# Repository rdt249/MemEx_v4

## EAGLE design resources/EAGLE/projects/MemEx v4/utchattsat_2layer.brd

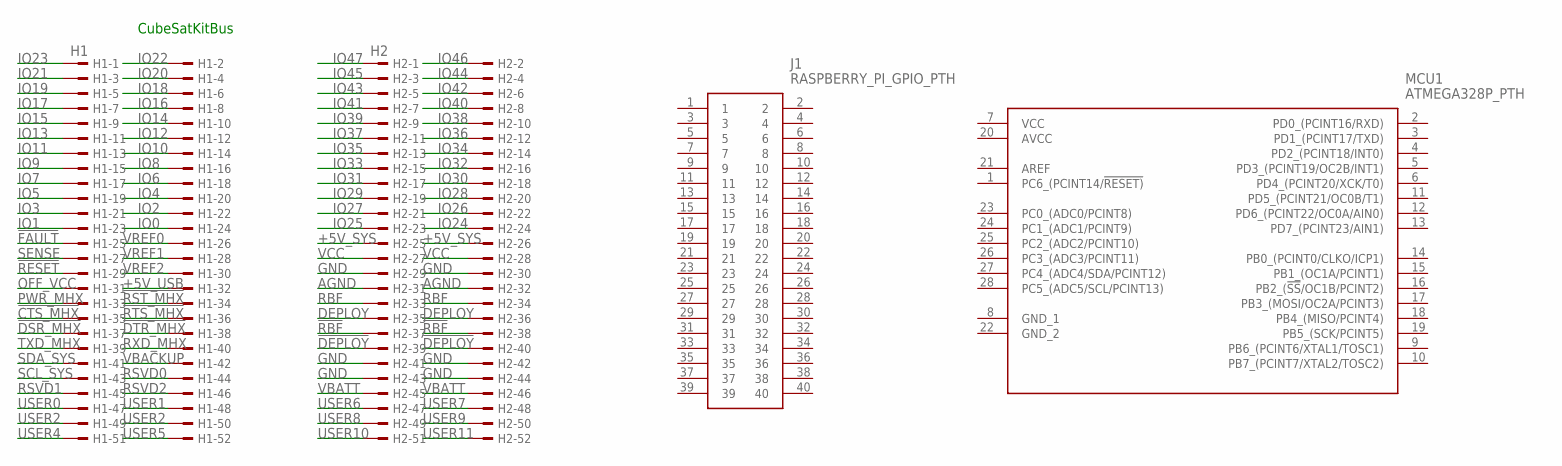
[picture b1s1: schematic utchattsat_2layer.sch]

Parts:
H1: H1; TSW-126-XX-G-D
H2: H2; TSW-126-XX-G-D
J1: RASPBERRY_PI_GPIO_PTH; RHDR40W64P254_2X20_5130X500X13
MCU1: ATMEGA328P_PTH; DIP794W53P254L3467H457Q28N

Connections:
!CTS_MHX: H1.35
!DEPLOY: H2.39, H2.40
!DSR_MHX: H1.37
!DTR_MHX: H1.38
!FAULT: H1.25
!RBF: H2.37, H2.38
!RESET: H1.29
!RST_MHX: H1.34
!RTS_MHX: H1.36
+5V_SYS: H2.25, H2.26
+5V_USB: H1.32
AGND: H2.31, H2.32
DEPLOY: H2.35, H2.36
GND: H2.29, H2.30, H2.41, H2.42, H2.43, H2.44
IO0: H1.24
IO1: H1.23
IO2: H1.22
IO3: H1.21
IO4: H1.20
IO5: H1.19
IO6: H1.18
IO7: H1.17
IO8: H1.16
IO9: H1.15
IO10: H1.14
IO11: H1.13
IO12: H1.12
IO13: H1.11
IO14: H1.10
IO15: H1.9
IO16: H1.8
IO17: H1.7
IO18: H1.6
IO19: H1.5
IO20: H1.4
IO21: H1.3
IO22: H1.2
IO23: H1.1
IO24: H2.24
IO25: H2.23
IO26: H2.22
IO27: H2.21
IO28: H2.20
IO29: H2.19
IO30: H2.18
IO31: H2.17
IO32: H2.16
IO33: H2.15
IO34: H2.14
IO35: H2.13
IO36: H2.12
IO37: H2.11
IO38: H2.10
IO39: H2.9
IO40: H2.8
IO41: H2.7
IO42: H2.6
IO43: H2.5
IO44: H2.4
IO45: H2.3
IO46: H2.2
IO47: H2.1
OFF_VCC: H1.31
PWR_MHX: H1.33
RBF: H2.33, H2.34
RSVD0: H1.44
RSVD1: H1.45
RSVD2: H1.46
RXD_MHX: H1.40
SCL_SYS: H1.43
SDA_SYS: H1.41
SENSE: H1.27
TXD_MHX: H1.39
USER0: H1.47
USER1: H1.48
USER2: H1.49, H1.50
USER4: H1.51
USER5: H1.52
USER6: H2.47
USER7: H2.48
USER8: H2.49
USER9: H2.50
USER10: H2.51
USER11: H2.52
VBACKUP: H1.42
VBATT: H2.45, H2.46
VCC: H2.27, H2.28
VREF0: H1.26
VREF1: H1.28
VREF2: H1.30

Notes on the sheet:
CubeSatKitBus

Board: 2 copper layers, 4 parts (2 on the bottom side), 10 nets, no tracks yet.

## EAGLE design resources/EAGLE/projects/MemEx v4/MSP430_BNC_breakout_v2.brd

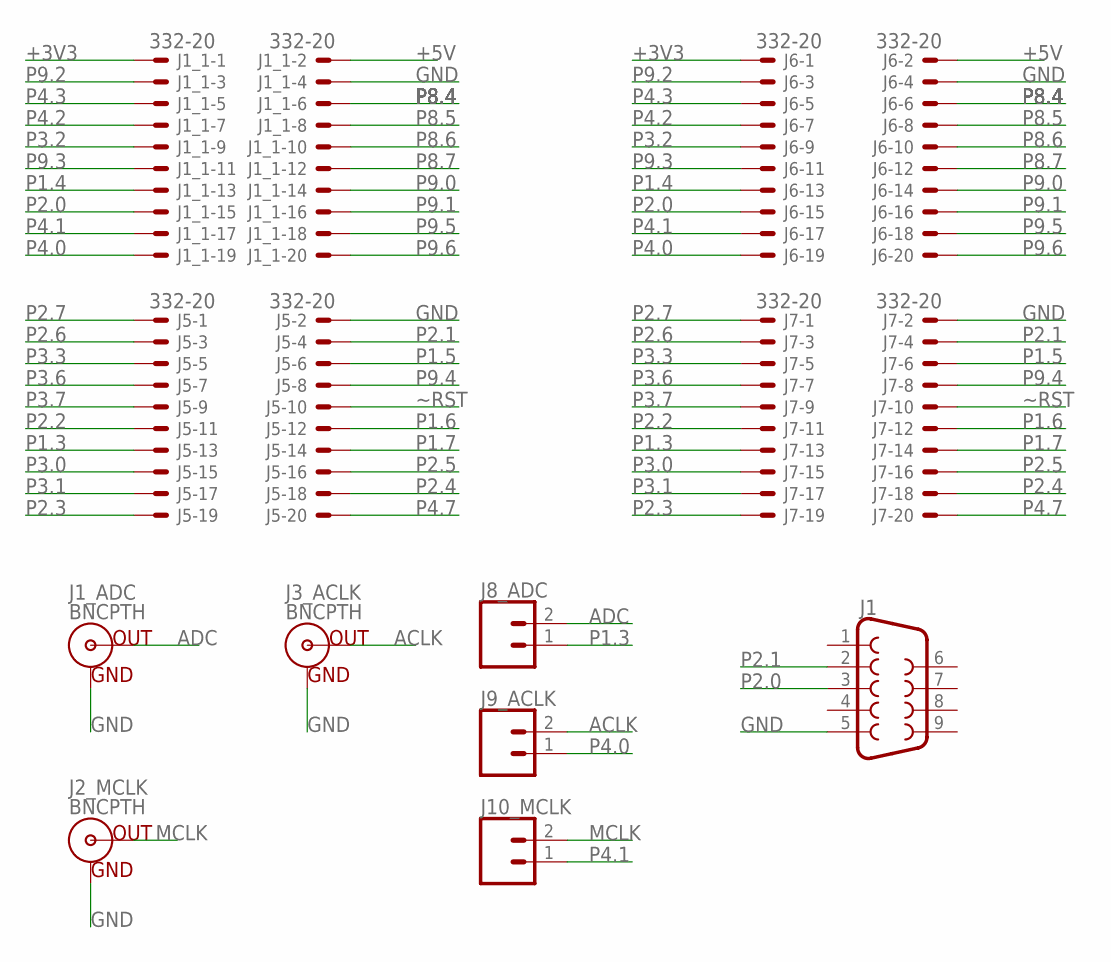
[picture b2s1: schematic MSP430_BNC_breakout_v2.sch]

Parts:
J1: DB9FEMALE; DB9
J1_1, J5, J6, J7: 332-20
J1_ADC, J2_MCLK, J3_ACLK: BNCPTH; BNC
J8_ADC, J9_ACLK, J10_MCLK: CONN_02; 1X02

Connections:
+3V3: J1_1.1, J6.1
+5V: J1_1.2, J6.2
ACLK: J3_ACLK.S (OUT), J9_ACLK.2
ADC: J1_ADC.S (OUT), J8_ADC.2
GND: J1.5, J1_1.4, J1_ADC.GND, J2_MCLK.GND, J3_ACLK.GND, J5.2, J6.4, J7.2
MCLK: J2_MCLK.S (OUT), J10_MCLK.2
P1.3: J5.13, J7.13, J8_ADC.1
P1.4: J1_1.13, J6.13
P1.5: J5.6, J7.6
P1.6: J5.12, J7.12
P1.7: J5.14, J7.14
P2.0: J1.3, J1_1.15, J6.15
P2.1: J1.2, J5.4, J7.4
P2.2: J5.11, J7.11
P2.3: J5.19, J7.19
P2.4: J5.18, J7.18
P2.5: J5.16, J7.16
P2.6: J5.3, J7.3
P2.7: J5.1, J7.1
P3.0: J5.15, J7.15
P3.1: J5.17, J7.17
P3.2: J1_1.9, J6.9
P3.3: J5.5, J7.5
P3.6: J5.7, J7.7
P3.7: J5.9, J7.9
P4.0: J1_1.19, J6.19, J9_ACLK.1
P4.1: J1_1.17, J6.17, J10_MCLK.1
P4.2: J1_1.7, J6.7
P4.3: J1_1.5, J6.5
P4.7: J5.20, J7.20
P8.4: J1_1.6, J6.6
P8.5: J1_1.8, J6.8
P8.6: J1_1.10, J6.10
P8.7: J1_1.12, J6.12
P9.0: J1_1.14, J6.14
P9.1: J1_1.16, J6.16
P9.2: J1_1.3, J6.3
P9.3: J1_1.11, J6.11
P9.4: J5.8, J7.8
P9.5: J1_1.18, J6.18
P9.6: J1_1.20, J6.20
~RST: J5.10, J7.10

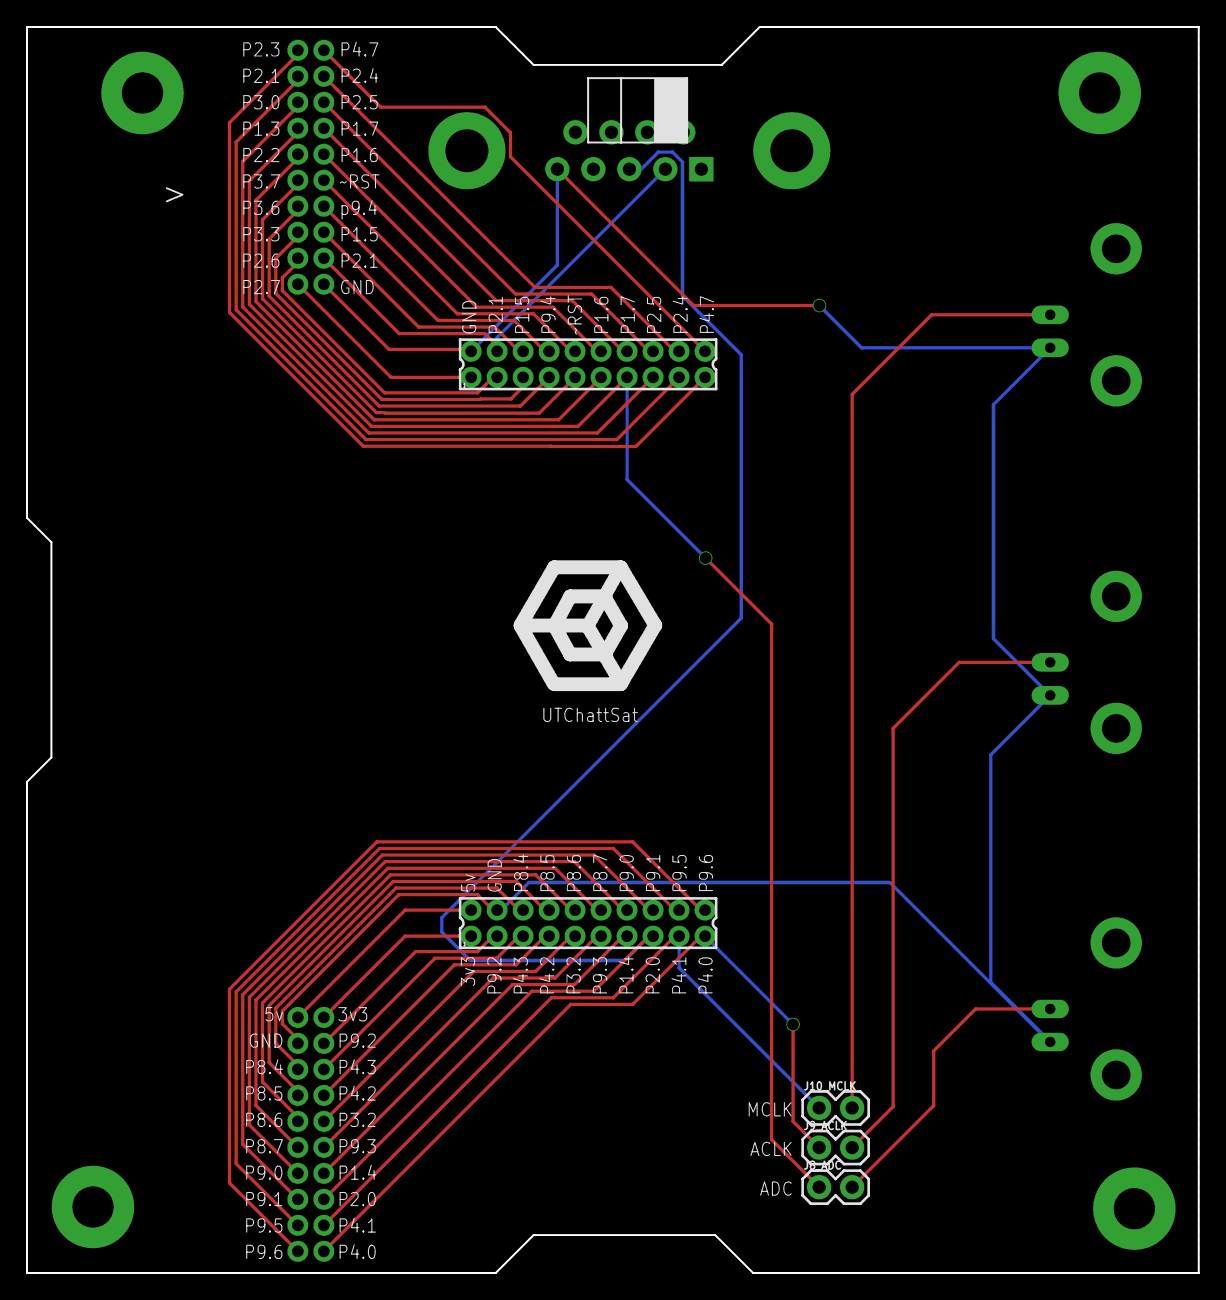
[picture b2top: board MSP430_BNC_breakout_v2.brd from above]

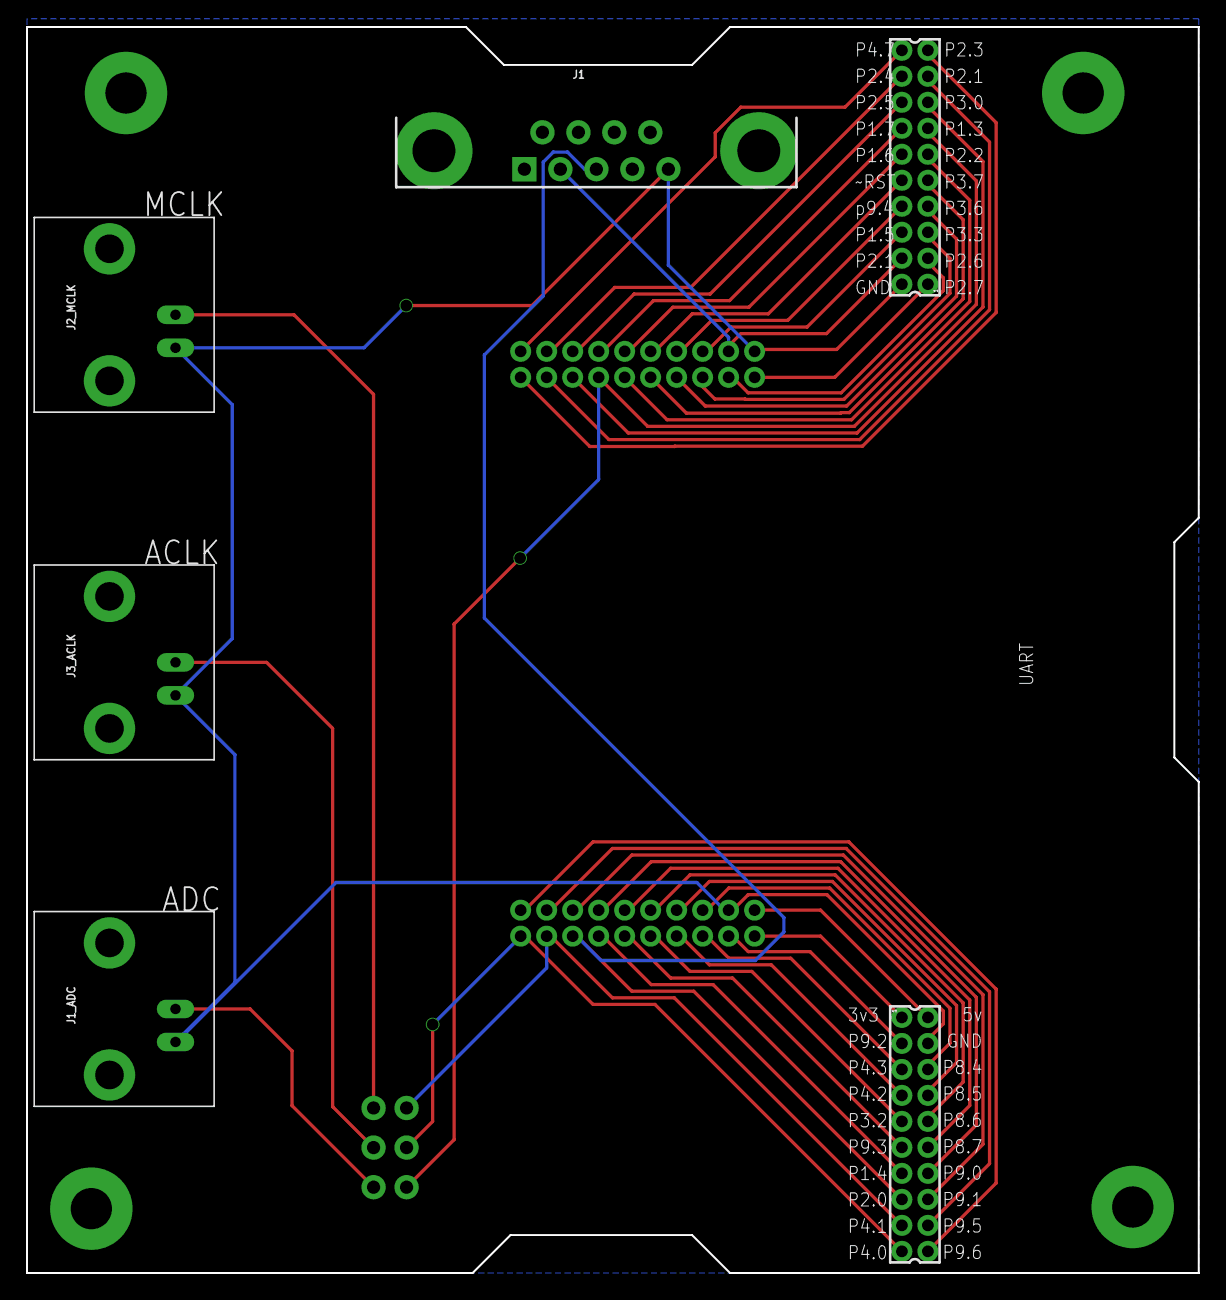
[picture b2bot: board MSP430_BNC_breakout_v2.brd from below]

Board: 2 copper layers, 90.2 x 95.9 mm, 11 parts (6 on the bottom side), 42 nets.

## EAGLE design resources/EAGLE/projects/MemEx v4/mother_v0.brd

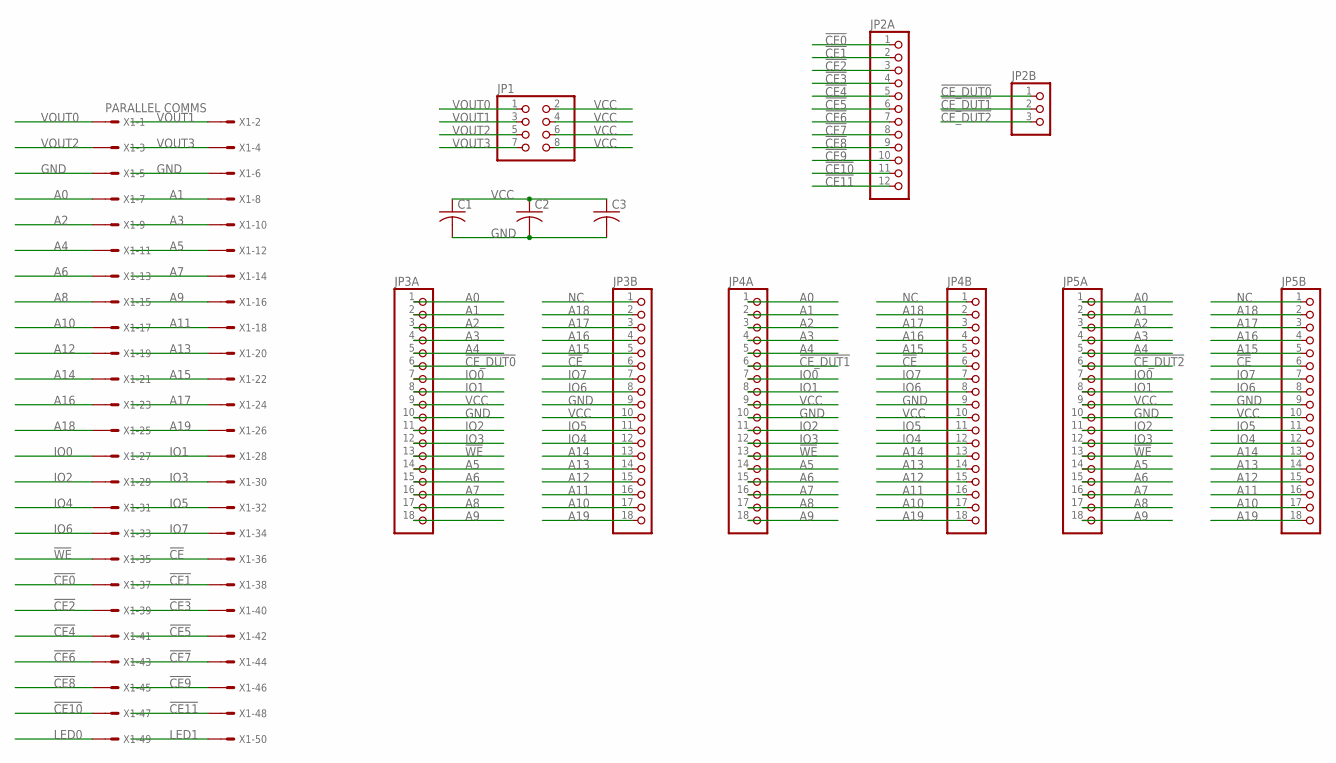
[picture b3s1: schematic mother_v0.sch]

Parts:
C1, C2, C3: C-USC0805; C0805
JP1: PINHD-2X4; 2X04
JP2A: PINHD-1X12; 1X12
JP2B: PINHD-1X3; 1X03
JP3A, JP3B, JP4A, JP4B, JP5A, JP5B: PINHD-1X18; 1X18
X1: PARALLEL COMMS; 057-050-1

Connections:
!CE: JP3B.6, JP4B.6, JP5B.6, X1.36
!CE0: JP2A.1, X1.37
!CE1: JP2A.2, X1.38
!CE2: JP2A.3, X1.39
!CE3: JP2A.4, X1.40
!CE4: JP2A.5, X1.41
!CE5: JP2A.6, X1.42
!CE6: JP2A.7, X1.43
!CE7: JP2A.8, X1.44
!CE8: JP2A.9, X1.45
!CE9: JP2A.10, X1.46
!CE10: JP2A.11, X1.47
!CE11: JP2A.12, X1.48
!CE_DUT0: JP2B.1, JP3A.6
!CE_DUT1: JP2B.2, JP4A.6
!CE_DUT2: JP2B.3, JP5A.6
!WE: JP3A.13, JP4A.13, JP5A.13, X1.35
A0: JP3A.1, JP4A.1, JP5A.1, X1.7
A1: JP3A.2, JP4A.2, JP5A.2, X1.8
A2: JP3A.3, JP4A.3, JP5A.3, X1.9
A3: JP3A.4, JP4A.4, JP5A.4, X1.10
A4: JP3A.5, JP4A.5, JP5A.5, X1.11
A5: JP3A.14, JP4A.14, JP5A.14, X1.12
A6: JP3A.15, JP4A.15, JP5A.15, X1.13
A7: JP3A.16, JP4A.16, JP5A.16, X1.14
A8: JP3A.17, JP4A.17, JP5A.17, X1.15
A9: JP3A.18, JP4A.18, JP5A.18, X1.16
A10: JP3B.17, JP4B.17, JP5B.17, X1.17
A11: JP3B.16, JP4B.16, JP5B.16, X1.18
A12: JP3B.15, JP4B.15, JP5B.15, X1.19
A13: JP3B.14, JP4B.14, JP5B.14, X1.20
A14: JP3B.13, JP4B.13, JP5B.13, X1.21
A15: JP3B.5, JP4B.5, JP5B.5, X1.22
A16: JP3B.4, JP4B.4, JP5B.4, X1.23
A17: JP3B.3, JP4B.3, JP5B.3, X1.24
A18: JP3B.2, JP4B.2, JP5B.2, X1.25
A19: JP3B.18, JP4B.18, JP5B.18, X1.26
GND: C1.2, C2.2, C3.2, JP3A.10, JP3B.9, JP4A.10, JP4B.9, JP5A.10, JP5B.9, X1.5, X1.6
IO0: JP3A.7, JP4A.7, JP5A.7, X1.27
IO1: JP3A.8, JP4A.8, JP5A.8, X1.28
IO2: JP3A.11, JP4A.11, JP5A.11, X1.29
IO3: JP3A.12, JP4A.12, JP5A.12, X1.30
IO4: JP3B.12, JP4B.12, JP5B.12, X1.31
IO5: JP3B.11, JP4B.11, JP5B.11, X1.32
IO6: JP3B.8, JP4B.8, JP5B.8, X1.33
IO7: JP3B.7, JP4B.7, JP5B.7, X1.34
LED0: X1.49
LED1: X1.50
NC: JP3B.1, JP4B.1, JP5B.1
VCC: C1.1, C2.1, C3.1, JP1.2, JP1.4, JP1.6, JP1.8, JP3A.9, JP3B.10, JP4A.9, JP4B.10, JP5A.9, JP5B.10
VOUT0: JP1.1, X1.1
VOUT1: JP1.3, X1.2
VOUT2: JP1.5, X1.3
VOUT3: JP1.7, X1.4

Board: 2 copper layers, 13 parts (0 on the bottom side), 52 nets, no tracks yet.

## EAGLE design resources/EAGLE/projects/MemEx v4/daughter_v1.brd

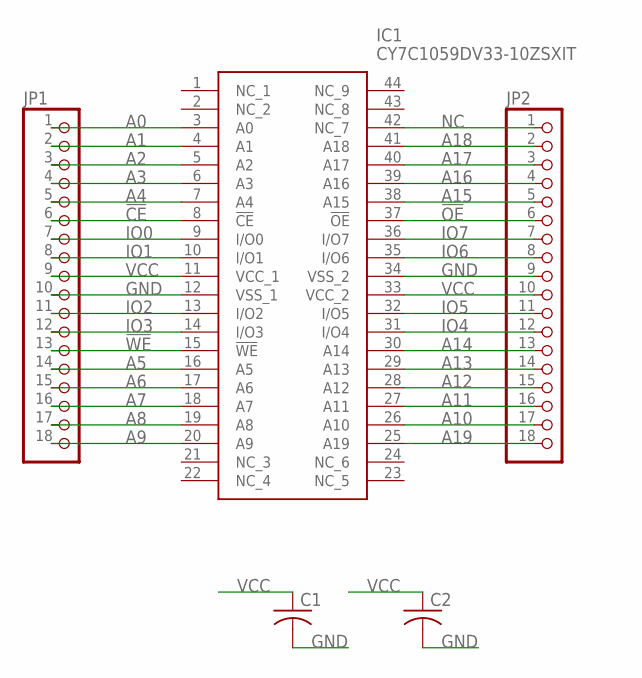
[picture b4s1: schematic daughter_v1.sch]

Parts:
C1, C2: C-USC0805; C0805
IC1: CY7C1059DV33-10ZSXIT; SOP80P1184X119-44N
JP1, JP2: PINHD-1X18; 1X18

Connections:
!CE: IC1.8 (!CE), JP1.6
!OE: IC1.37 (!OE), JP2.6
!WE: IC1.15 (!WE), JP1.13
A0: IC1.3 (A0), JP1.1
A1: IC1.4 (A1), JP1.2
A2: IC1.5 (A2), JP1.3
A3: IC1.6 (A3), JP1.4
A4: IC1.7 (A4), JP1.5
A5: IC1.16 (A5), JP1.14
A6: IC1.17 (A6), JP1.15
A7: IC1.18 (A7), JP1.16
A8: IC1.19 (A8), JP1.17
A9: IC1.20 (A9), JP1.18
A10: IC1.26 (A10), JP2.17
A11: IC1.27 (A11), JP2.16
A12: IC1.28 (A12), JP2.15
A13: IC1.29 (A13), JP2.14
A14: IC1.30 (A14), JP2.13
A15: IC1.38 (A15), JP2.5
A16: IC1.39 (A16), JP2.4
A17: IC1.40 (A17), JP2.3
A18: IC1.41 (A18), JP2.2
A19: IC1.25 (A19), JP2.18
GND: C1.2, C2.2, IC1.12 (VSS_1), IC1.34 (VSS_2), JP1.10, JP2.9
IO0: IC1.9 (I/O0), JP1.7
IO1: IC1.10 (I/O1), JP1.8
IO2: IC1.13 (I/O2), JP1.11
IO3: IC1.14 (I/O3), JP1.12
IO4: IC1.31 (I/O4), JP2.12
IO5: IC1.32 (I/O5), JP2.11
IO6: IC1.35 (I/O6), JP2.8
IO7: IC1.36 (I/O7), JP2.7
NC: IC1.42 (NC_7), JP2.1
VCC: C1.1, C2.1, IC1.11 (VCC_1), IC1.33 (VCC_2), JP1.9, JP2.10

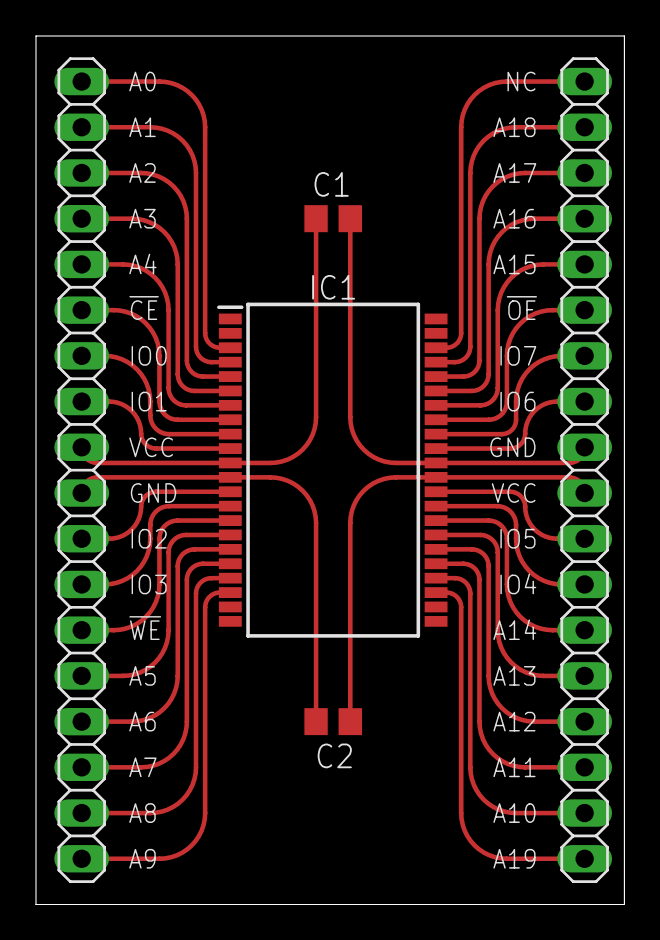
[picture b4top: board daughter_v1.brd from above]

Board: 2 copper layers, 32.7 x 48.2 mm, 5 parts (0 on the bottom side), 34 nets.

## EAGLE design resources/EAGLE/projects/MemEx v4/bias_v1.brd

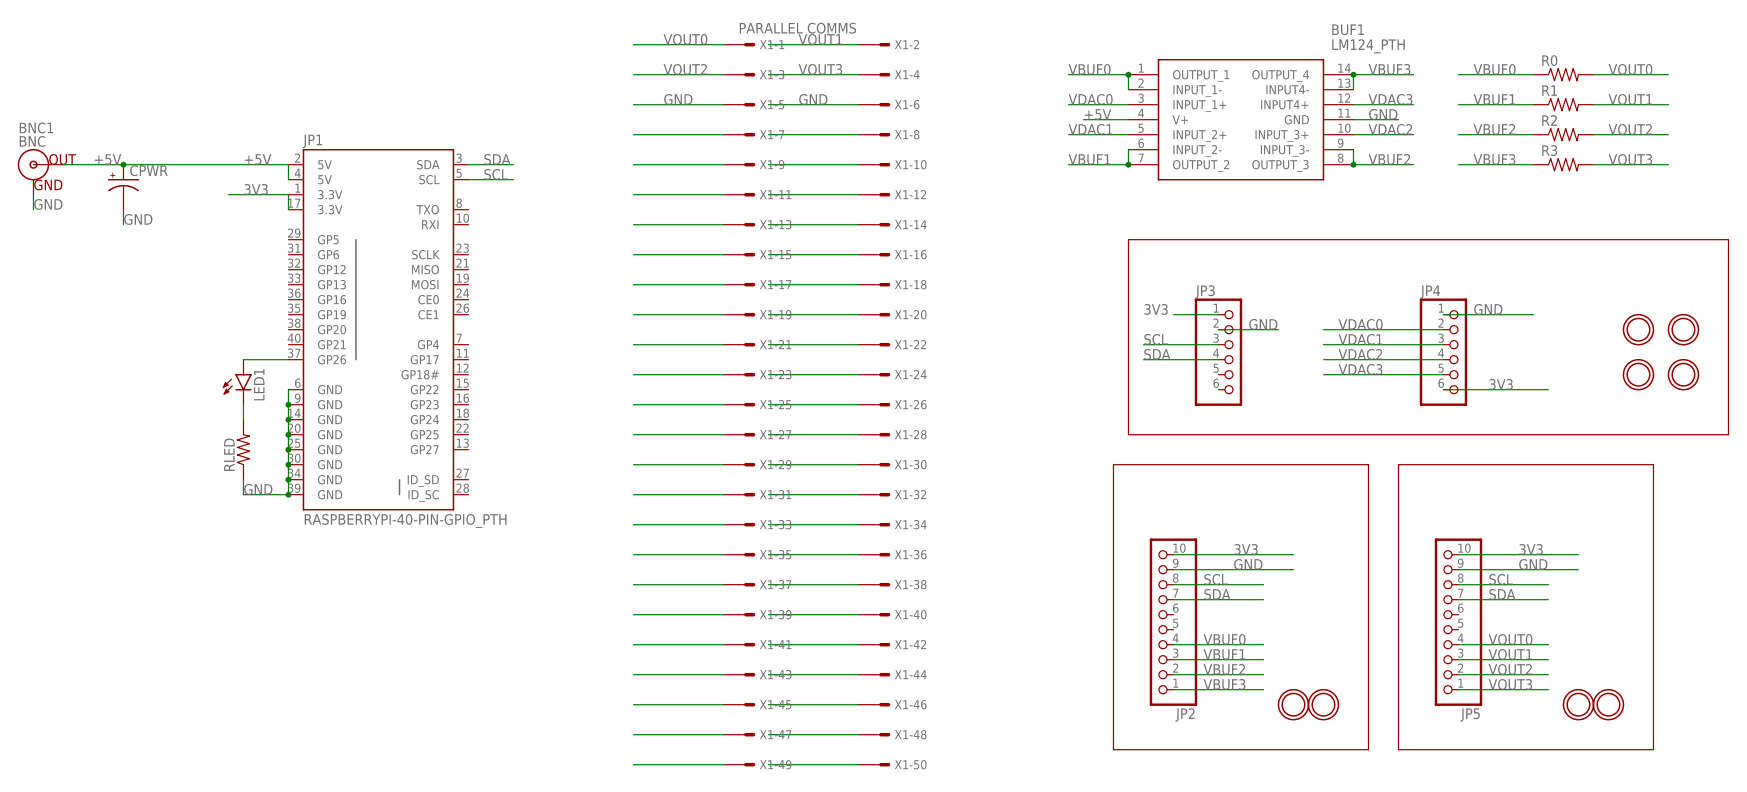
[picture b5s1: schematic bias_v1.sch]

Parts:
BNC1: BNC
BUF1: LM124_PTH; CDIP790W66P254L1954H508Q14
CPWR: CPOL-USE2.5-6; E2,5-6
JP1: RASPBERRYPI-40-PIN-GPIO_PTH; 2X20_SHROUDED
JP2, JP5: HEADER-1X1070MIL; 1X10_ROUND70
JP3, JP4: HEADER-1X670MIL; 1X06_ROUND_70
LED1: LED3MM
R0, R1, R2, R3: R-US_0204/7; 0204/7
RLED: R-US_0204/7; 0204/7
U$3, U$4, U$5, U$6, U$7, U$8, U$15, U$16: MOUNTINGHOLE2.5; MOUNTINGHOLE_2.5_PLATED
X1: PARALLEL COMMS; 057-050-1

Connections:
3V3: JP1.1 (3.3V), JP1.17 (3.3V), JP2.10, JP3.1, JP4.6, JP5.10
+5V: BNC1.S (OUT), BUF1.4 (V+), CPWR.+, JP1.2 (5V), JP1.4 (5V)
GND: BNC1.GND, BUF1.11 (GND), CPWR.-, JP1.6 (GND), JP1.9 (GND), JP1.14 (GND), JP1.20 (GND), JP1.25 (GND), JP1.30 (GND), JP1.34 (GND), JP1.39 (GND), JP2.9, JP3.2, JP4.1, JP5.9, RLED.1, X1.5, X1.6
unnamed: JP1.37 (GP26), LED1.A
unnamed: LED1.K (C), RLED.2
SCL: JP1.5 (SCL), JP2.8, JP3.3, JP5.8
SDA: JP1.3 (SDA), JP2.7, JP3.4, JP5.7
VBUF0: BUF1.1 (OUTPUT_1), BUF1.2 (INPUT_1-), JP2.4, R0.1
VBUF1: BUF1.6 (INPUT_2-), BUF1.7 (OUTPUT_2), JP2.3, R1.1
VBUF2: BUF1.8 (OUTPUT_3), BUF1.9 (INPUT_3-), JP2.2, R2.1
VBUF3: BUF1.13 (INPUT4-), BUF1.14 (OUTPUT_4), JP2.1, R3.1
VDAC0: BUF1.3 (INPUT_1+), JP4.2
VDAC1: BUF1.5 (INPUT_2+), JP4.3
VDAC2: BUF1.10 (INPUT_3+), JP4.4
VDAC3: BUF1.12 (INPUT4+), JP4.5
VOUT0: JP5.4, R0.2, X1.1
VOUT1: JP5.3, R1.2, X1.2
VOUT2: JP5.2, R2.2, X1.3
VOUT3: JP5.1, R3.2, X1.4

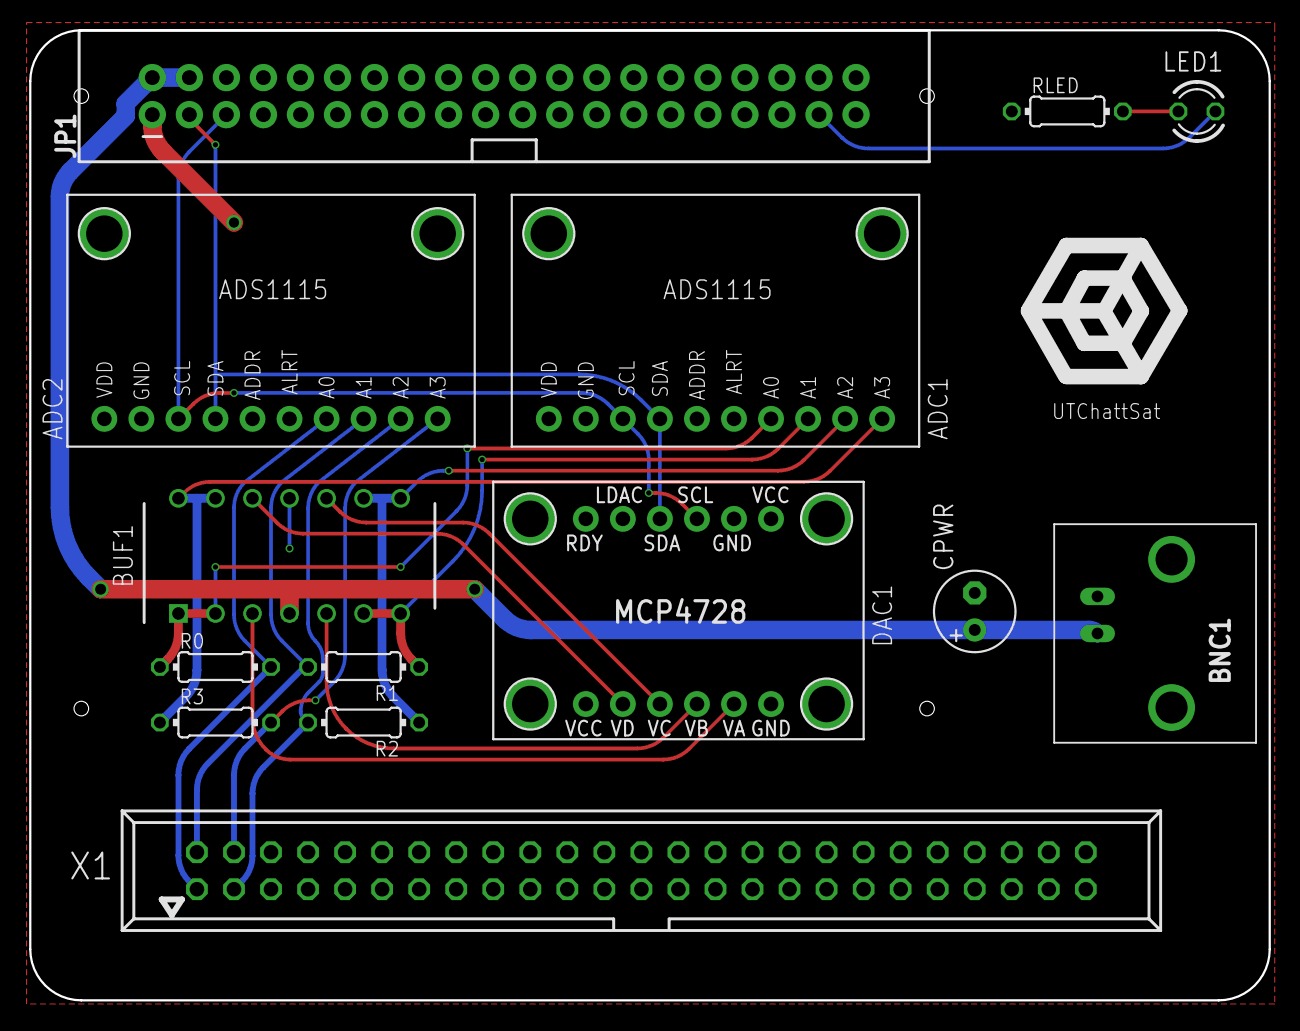
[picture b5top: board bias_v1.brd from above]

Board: 2 copper layers, 85.0 x 66.5 mm, 23 parts (0 on the bottom side), 19 nets.

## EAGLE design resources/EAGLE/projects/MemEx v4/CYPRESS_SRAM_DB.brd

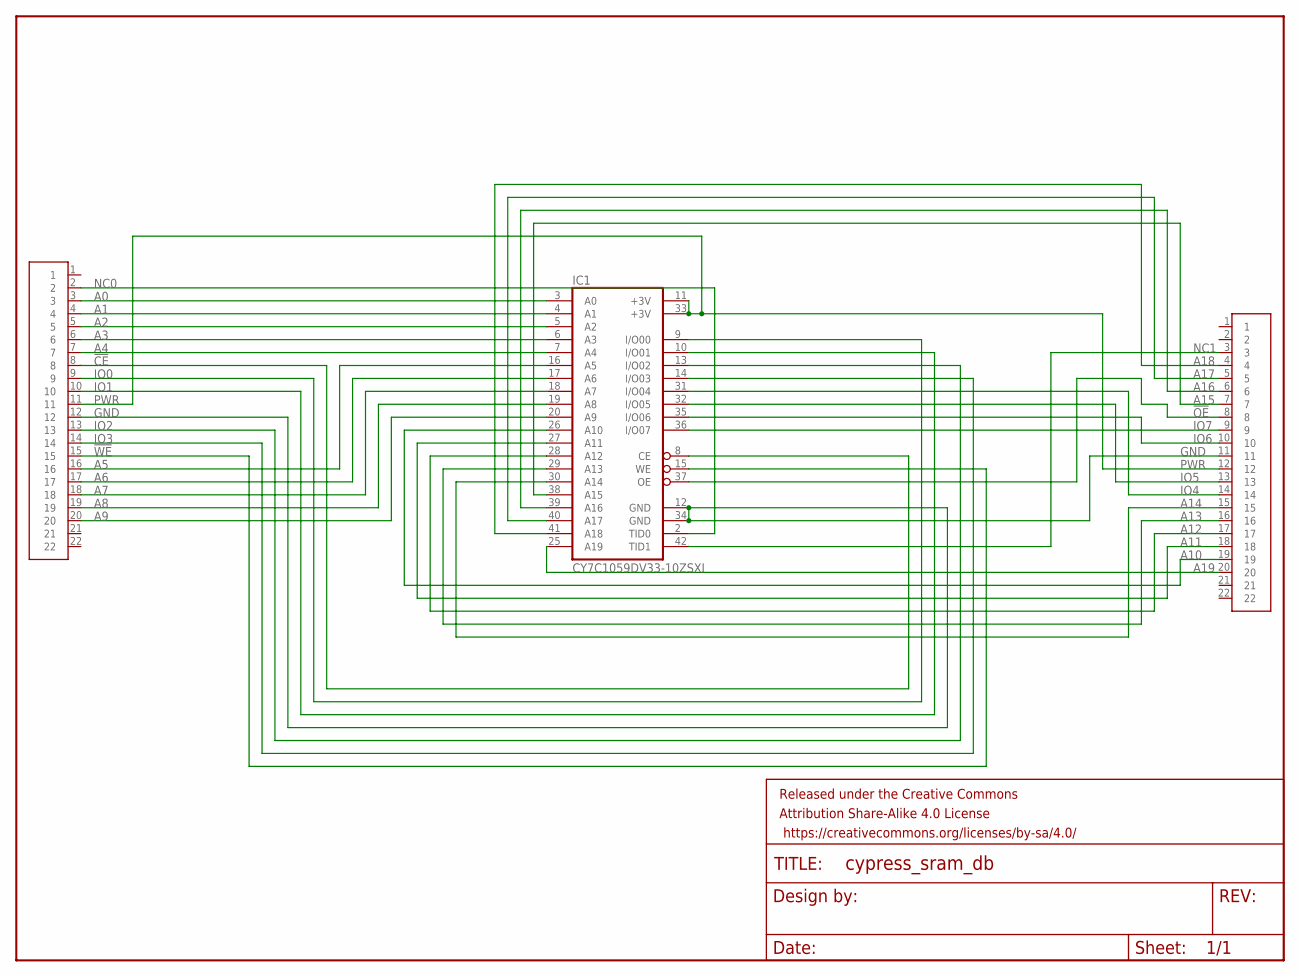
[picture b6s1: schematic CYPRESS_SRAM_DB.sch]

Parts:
FRAME1: FRAME-LETTERNO_PACKAGE; DUMMY
IC1: CY7C1059DV33-10ZSXI; TSOPII-Z44
U$1, U$2: 1X22THM; 1X22

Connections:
!CE: IC1.8 (CE), U$2.8
!OE: IC1.37 (OE), U$1.8
!WE: IC1.15 (WE), U$2.15
A0: IC1.3 (A0), U$2.3
A1: IC1.4 (A1), U$2.4
A2: IC1.5 (A2), U$2.5
A3: IC1.6 (A3), U$2.6
A4: IC1.7 (A4), U$2.7
A5: IC1.16 (A5), U$2.16
A6: IC1.17 (A6), U$2.17
A7: IC1.18 (A7), U$2.18
A8: IC1.19 (A8), U$2.19
A9: IC1.20 (A9), U$2.20
A10: IC1.26 (A10), U$1.19
A11: IC1.27 (A11), U$1.18
A12: IC1.28 (A12), U$1.17
A13: IC1.29 (A13), U$1.16
A14: IC1.30 (A14), U$1.15
A15: IC1.38 (A15), U$1.7
A16: IC1.39 (A16), U$1.6
A17: IC1.40 (A17), U$1.5
A18: IC1.41 (A18), U$1.4
A19: IC1.25 (A19), U$1.20
GND: IC1.12 (GND), IC1.34 (GND), U$1.11, U$2.12
IO0: IC1.9 (I/O00), U$2.9
IO1: IC1.10 (I/O01), U$2.10
IO2: IC1.13 (I/O02), U$2.13
IO3: IC1.14 (I/O03), U$2.14
IO4: IC1.31 (I/O04), U$1.14
IO5: IC1.32 (I/O05), U$1.13
IO6: IC1.35 (I/O06), U$1.10
IO7: IC1.36 (I/O07), U$1.9
NC0: IC1.2 (TID0), U$2.2
NC1: IC1.42 (TID1), U$1.3
PWR: IC1.11 (+3V), IC1.33 (+3V), U$1.12, U$2.11

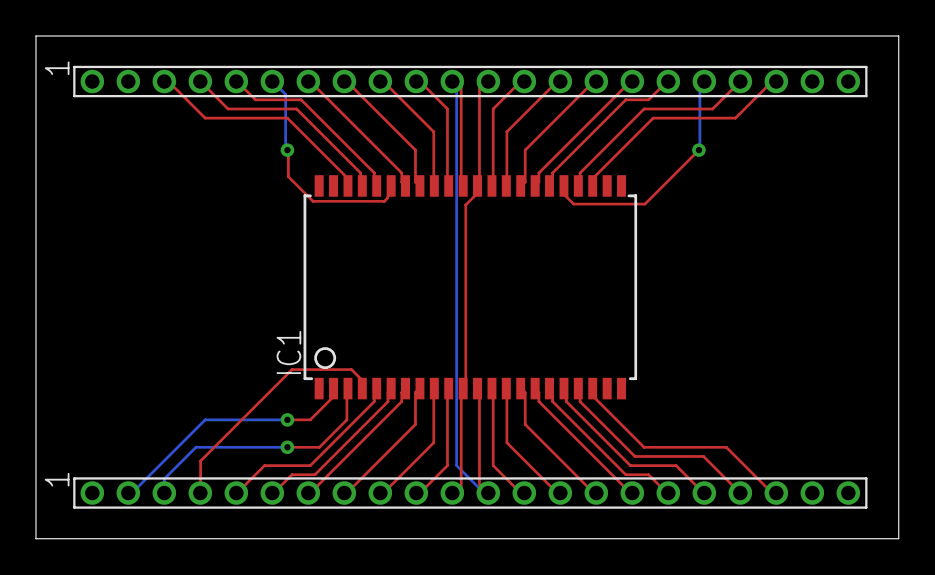
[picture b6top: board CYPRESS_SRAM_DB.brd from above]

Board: 2 copper layers, 47.9 x 27.9 mm, 4 parts (0 on the bottom side), 35 nets.

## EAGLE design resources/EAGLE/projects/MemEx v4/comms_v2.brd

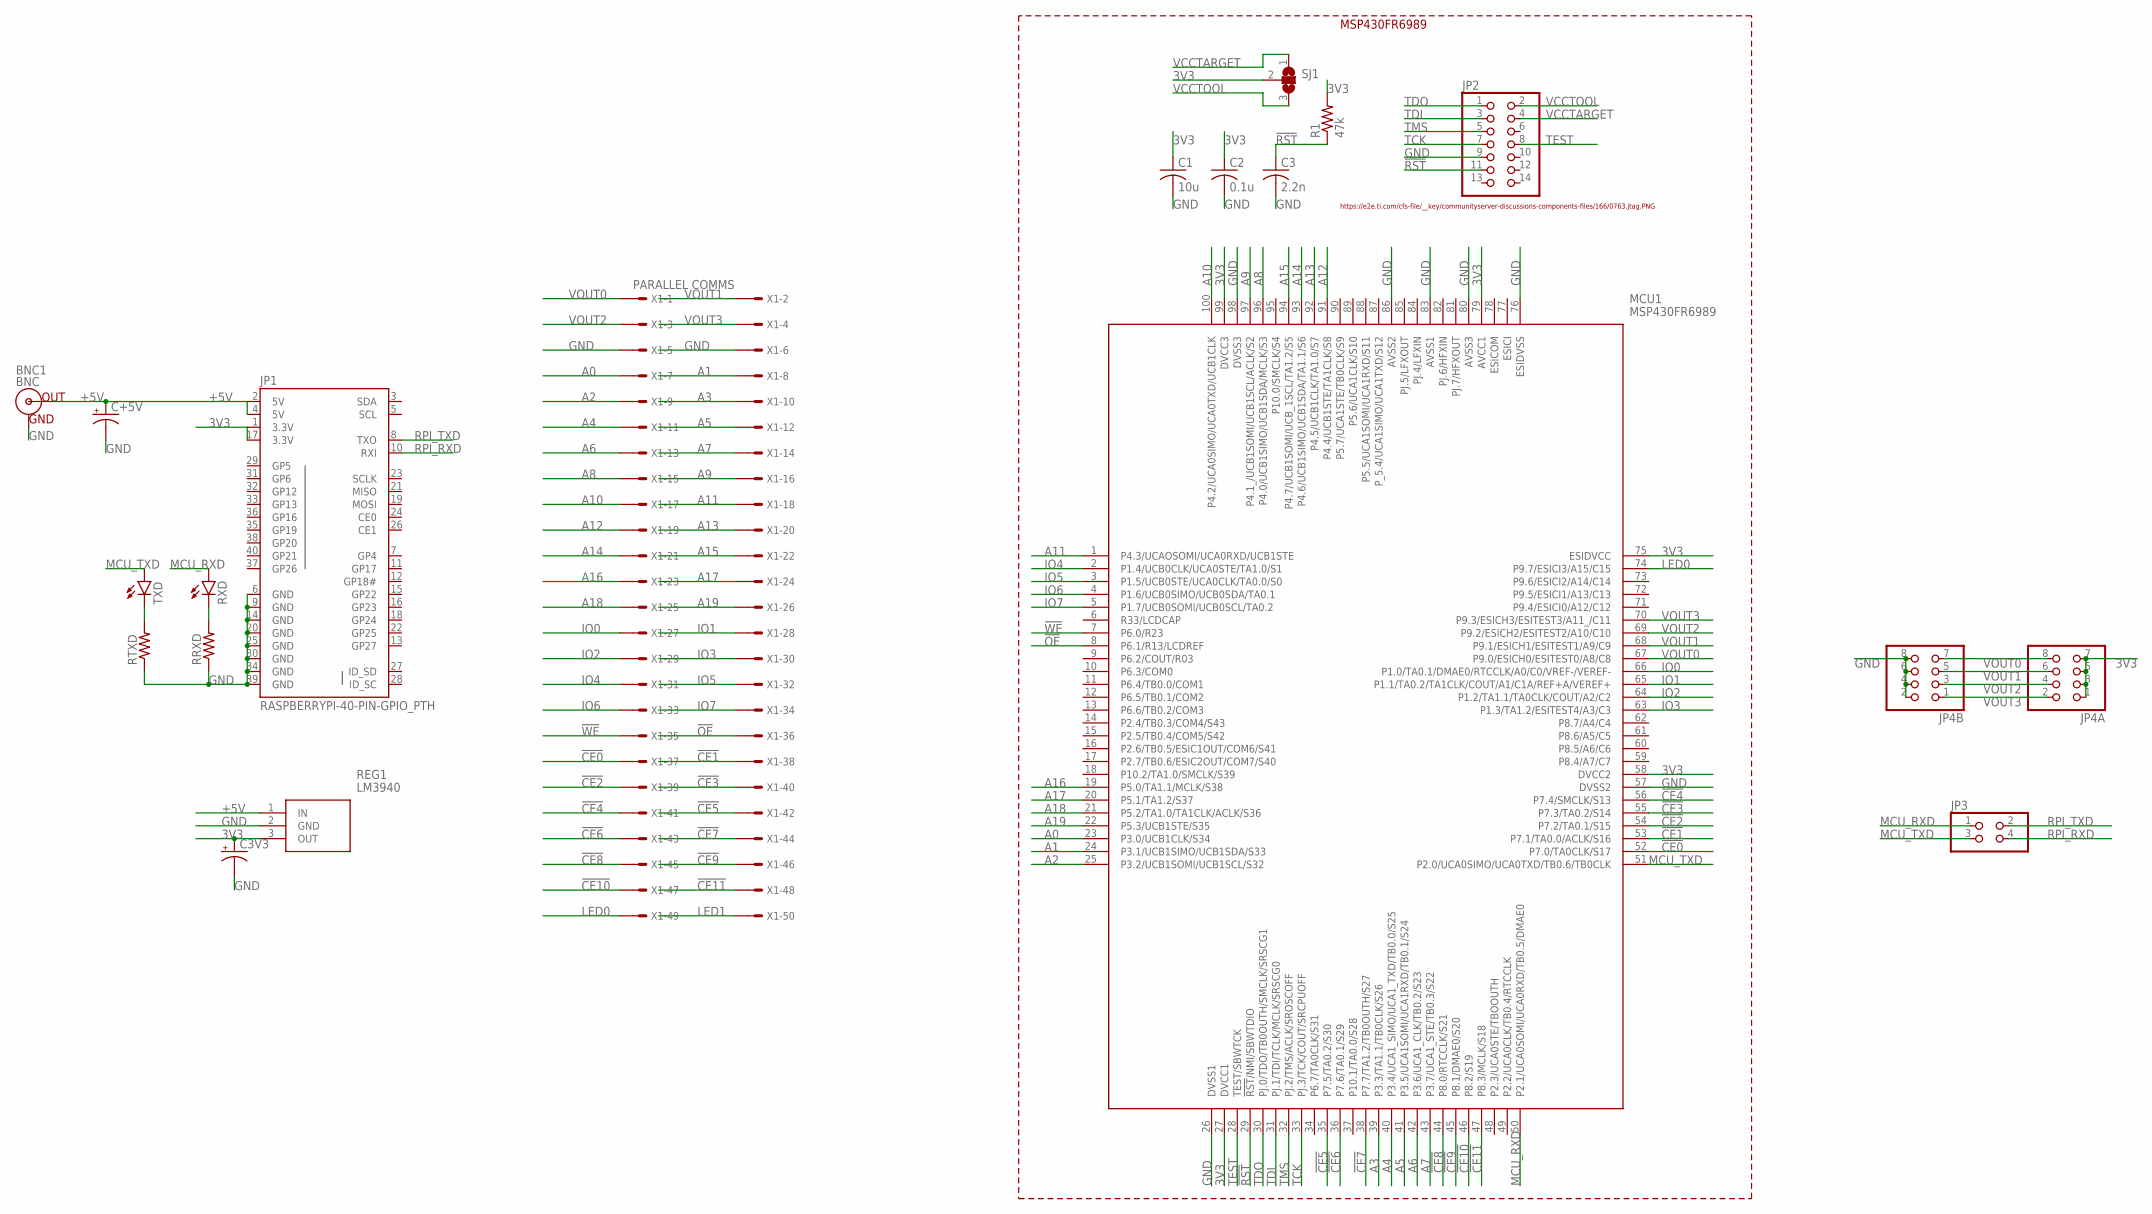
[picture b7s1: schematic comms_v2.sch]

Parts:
BNC1: BNC
C1: 10u; C0805
C2: 0.1u; C0805
C3: 2.2n; C0805
C3V3: CPOL-USE2.5-6; E2,5-6
C+5V: CPOL-USE2.5-6; E2,5-6
JP1: RASPBERRYPI-40-PIN-GPIO_PTH; 2X20_SHROUDED
JP2: PINHD-2X7; 2X07
JP3: PINHD-2X2; 2X02
JP4A, JP4B: PINHD-2X4; 2X04
MCU1: MSP430FR6989; QFP50P1600X1600X160-100N
R1: 47k; R0805
REG1: LM3940; TO254P470X1028X1955-3P
RRXD: R-US_0204/7; 0204/7
RTXD: R-US_0204/7; 0204/7
RXD: LED3MM
SJ1: SJ2W; SJ_2
TXD: LED3MM
X1: PARALLEL COMMS; 057-050-1

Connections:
3V3: C1.1, C2.1, C3V3.+, JP1.1 (3.3V), JP1.17 (3.3V), JP4A.1, JP4A.3, JP4A.5, JP4A.7, MCU1.27 (DVCC1), MCU1.58 (DVCC2), MCU1.75 (ESIDVCC), MCU1.79 (AVCC1), MCU1.99 (DVCC3), R1.2, REG1.3 (OUT), SJ1.2
!CE0: MCU1.52 (P7.0/TA0CLK/S17), X1.37
!CE1: MCU1.53 (P7.1/TA0.0/ACLK/S16), X1.38
!CE2: MCU1.54 (P7.2/TA0.1/S15), X1.39
!CE3: MCU1.55 (P7.3/TA0.2/S14), X1.40
!CE4: MCU1.56 (P7.4/SMCLK/S13), X1.41
!CE5: MCU1.35 (P7.5/TA0.2/S30), X1.42
!CE6: MCU1.36 (P7.6/TA0.1/S29), X1.43
!CE7: MCU1.38 (P7.7/TA1.2/TB0OUTH/S27), X1.44
!CE8: MCU1.44 (P8.0/RTCCLK/S21), X1.45
!CE9: MCU1.45 (P8.1/DMAE0/S20), X1.46
!CE10: MCU1.46 (P8.2/S19), X1.47
!CE11: MCU1.47 (P8.3/MCLK/S18), X1.48
!OE: MCU1.8 (P6.1/R13/LCDREF), X1.36
!RST: C3.1, JP2.11, MCU1.29 (!RST!/NMI/SBWTDIO), R1.1
!WE: MCU1.7 (P6.0/R23), X1.35
+5V: BNC1.S (OUT), C+5V.+, JP1.2 (5V), JP1.4 (5V), REG1.1 (IN)
A0: MCU1.23 (P3.0/UCB1CLK/S34), X1.7
A1: MCU1.24 (P3.1/UCB1SIMO/UCB1SDA/S33), X1.8
A2: MCU1.25 (P3.2/UCB1SOMI/UCB1SCL/S32), X1.9
A3: MCU1.39 (P3.3/TA1.1/TB0CLK/S26), X1.10
A4: MCU1.40 (P3.4/UCA1_SIMO/UCA1_TXD/TB0.0/S25), X1.11
A5: MCU1.41 (P3.5/UCA1SOMI/UCA1RXD/TB0.1/S24), X1.12
A6: MCU1.42 (P3.6/UCA1_CLK/TB0.2/S23), X1.13
A7: MCU1.43 (P3.7/UCA1_STE/TB0.3/S22), X1.14
A8: MCU1.96 (P4.0/UCB1SIMO/UCB1SDA/MCLK/S3), X1.15
A9: MCU1.97 (P4.1_/UCB1SOMI/UCB1SCL/ACLK/S2), X1.16
A10: MCU1.100 (P4.2/UCA0SIMO/UCA0TXD/UCB1CLK), X1.17
A11: MCU1.1 (P4.3/UCAOSOMI/UCA0RXD/UCB1STE), X1.18
A12: MCU1.91 (P4.4/UCB1STE/TA1CLK/S8), X1.19
A13: MCU1.92 (P4.5/UCB1CLK/TA1.0/S7), X1.20
A14: MCU1.93 (P4.6/UCB1SIMO/UCB1SDA/TA1.1/S6), X1.21
A15: MCU1.94 (P4.7/UCB1SOMI/UCB_1SCL/TA1.2/S5), X1.22
A16: MCU1.19 (P5.0/TA1.1/MCLK/S38), X1.23
A17: MCU1.20 (P5.1/TA1.2/S37), X1.24
A18: MCU1.21 (P5.2/TA1.0/TA1CLK/ACLK/S36), X1.25
A19: MCU1.22 (P5.3/UCB1STE/S35), X1.26
GND: BNC1.GND, C1.2, C2.2, C3.2, C3V3.-, C+5V.-, JP1.6 (GND), JP1.9 (GND), JP1.14 (GND), JP1.20 (GND), JP1.25 (GND), JP1.30 (GND), JP1.34 (GND), JP1.39 (GND), JP2.9, JP4B.2, JP4B.4, JP4B.6, JP4B.8, MCU1.26 (DVSS1), MCU1.57 (DVSS2), MCU1.76 (ESIDVSS), MCU1.80 (AVSS3), MCU1.83 (AVSS1), MCU1.86 (AVSS2), MCU1.98 (DVSS3), REG1.2 (GND), RRXD.1, RTXD.1, X1.5, X1.6
IO0: MCU1.66 (P1.0/TA0.1/DMAE0/RTCCLK/A0/C0/VREF-/VER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), X1.27
IO1: MCU1.65 (P1.1/TA0.2/TA1CLK/COUT/A1/C1A/REF+A/VER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), X1.28
IO2: MCU1.64 (P1.2/TA1.1/TA0CLK/COUT/A2/C2), X1.29
IO3: MCU1.63 (P1.3/TA1.2/ESITEST4/A3/C3), X1.30
IO4: MCU1.2 (P1.4/UCB0CLK/UCA0STE/TA1.0/S1), X1.31
IO5: MCU1.3 (P1.5/UCB0STE/UCA0CLK/TA0.0/S0), X1.32
IO6: MCU1.4 (P1.6/UCB0SIMO/UCB0SDA/TA0.1), X1.33
IO7: MCU1.5 (P1.7/UCB0SOMI/UCB0SCL/TA0.2), X1.34
LED0: MCU1.74 (P9.7/ESICI3/A15/C15), X1.49
LED1: X1.50
MCU_RXD: JP3.1, MCU1.50 (P2.1/UCA0SOMI/UCA0RXD/TB0.5/DMAE0), RXD.A
MCU_TXD: JP3.3, MCU1.51 (P2.0/UCA0SIMO/UCA0TXD/TB0.6/TB0CLK), TXD.A
unnamed: RTXD.2, TXD.K (C)
unnamed: RRXD.2, RXD.K (C)
RPI_RXD: JP1.10 (RXI), JP3.4
RPI_TXD: JP1.8 (TXO), JP3.2
TCK: JP2.7, MCU1.33 (PJ.3/TCK/COUT/SRCPUOFF)
TDI: JP2.3, MCU1.31 (PJ.1/TDI/TCLK/MCLK/SRSCG0)
TDO: JP2.1, MCU1.30 (PJ.0/TDO/TB0OUTH/SMCLK/SRSCG1)
TEST: JP2.8, MCU1.28 (TEST/SBWTCK)
TMS: JP2.5, MCU1.32 (PJ.2/TMS/ACLK/SROSCOFF)
VCCTARGET: JP2.4, SJ1.1
VCCTOOL: JP2.2, SJ1.3
VOUT0: JP4A.8, JP4B.7, MCU1.67 (P9.0/ESICH0/ESITEST0/A8/C8), X1.1
VOUT1: JP4A.6, JP4B.5, MCU1.68 (P9.1/ESICH1/ESITEST1/A9/C9), X1.2
VOUT2: JP4A.4, JP4B.3, MCU1.69 (P9.2/ESICH2/ESITEST2/A10/C10), X1.3
VOUT3: JP4A.2, JP4B.1, MCU1.70 (P9.3/ESICH3/ESITEST3/A11_/C11), X1.4

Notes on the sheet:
https://e2e.ti.com/cfs-file/__key/communityserver-discussions-components-files/166/0763.jtag.PNG
MSP430FR6989

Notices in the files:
parts and their libraries:
SparkFun-Aesthetics: Licensing: Creative Commons ShareAlike 4.0 International - https://creativecommons.org/licenses/by-sa/4.0
SparkFun-Aesthetics: Released under the Creative Commons Attribution Share-Alike 4.0 License
SparkFun-Aesthetics: https://creativecommons.org/licenses/by-sa/4.0
